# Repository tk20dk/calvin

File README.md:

# calvin
886 MHz Sensor module (CC1110)

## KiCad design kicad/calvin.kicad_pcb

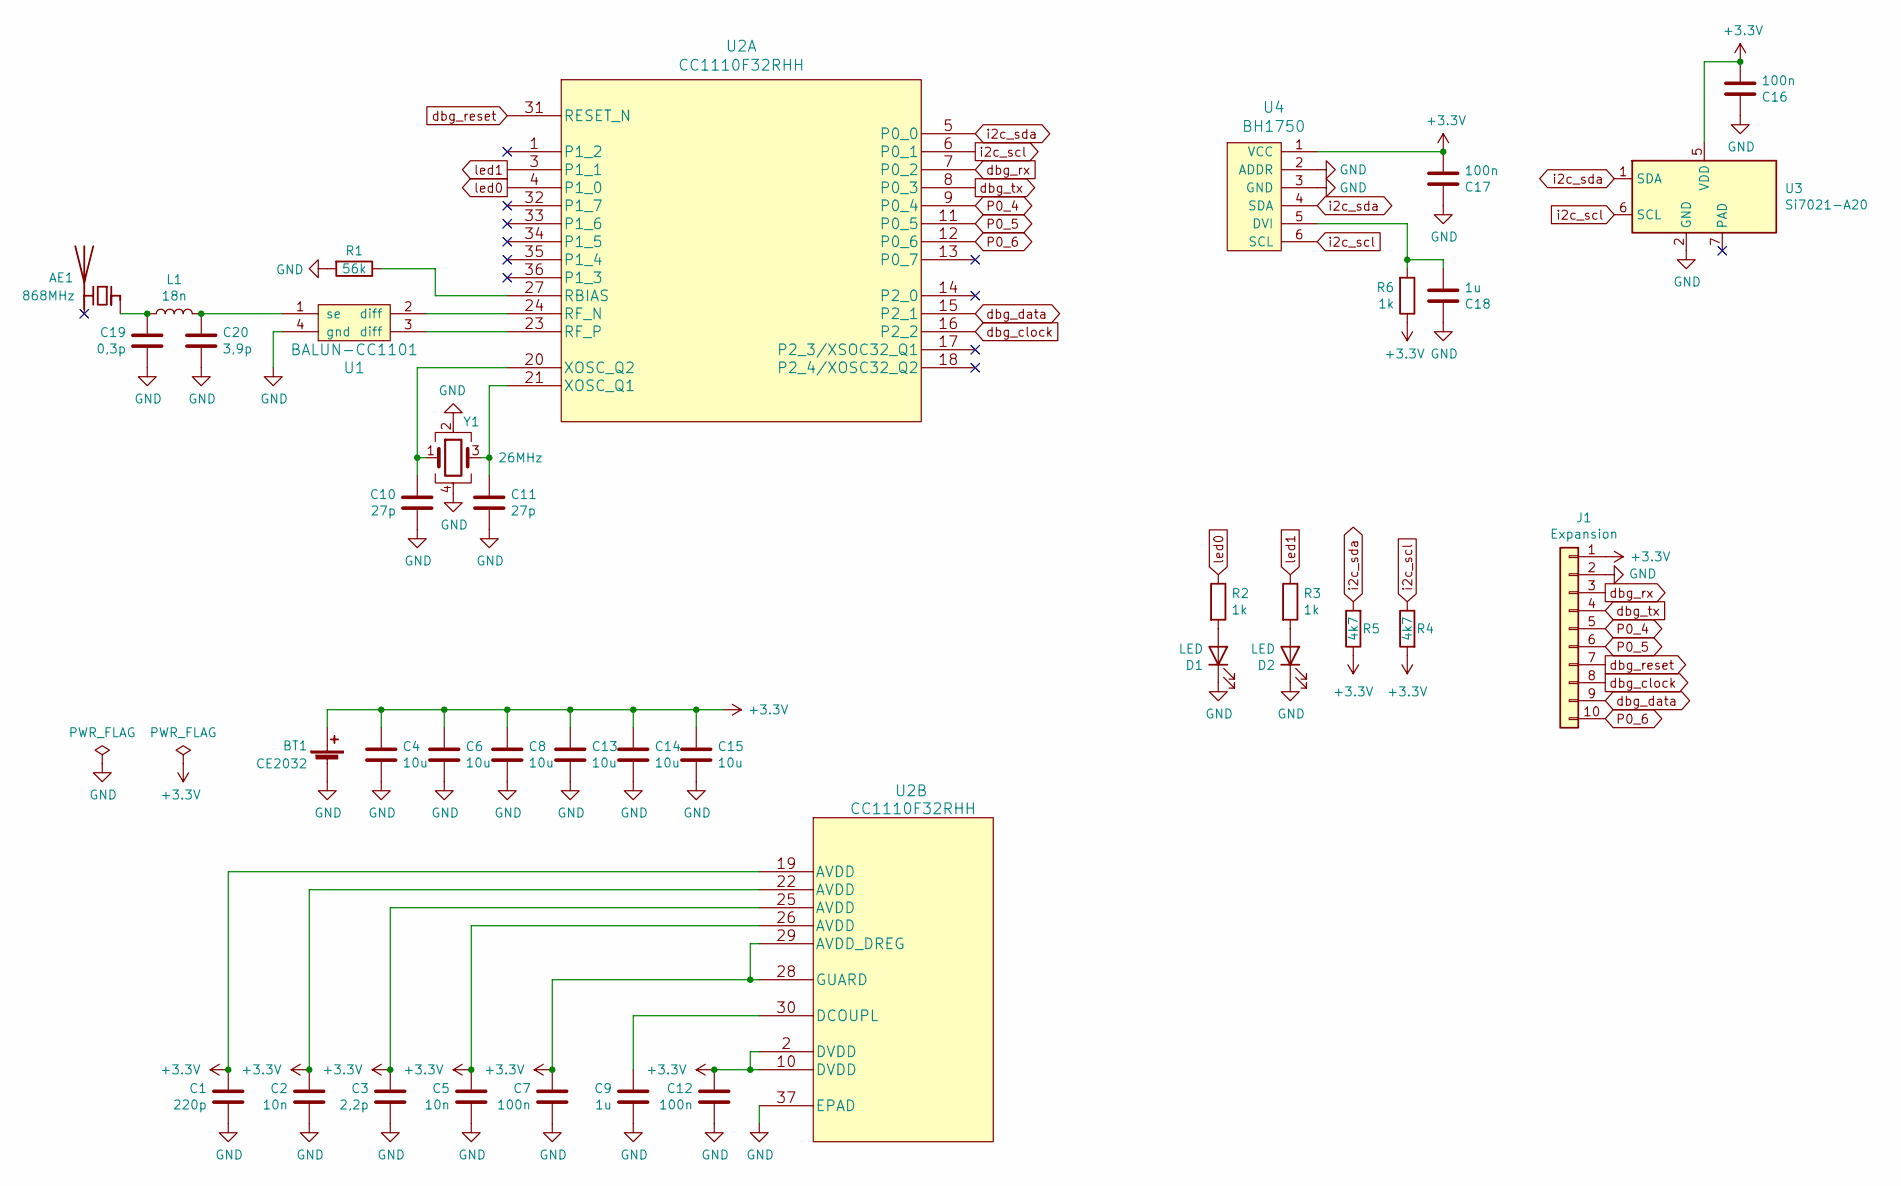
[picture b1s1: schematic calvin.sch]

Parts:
AE1: 868MHz; 0868AT43A0020
BT1: CE2032; CR2032_HOLDER_02
C1: 220p; C_0402_1005Metric
C2, C5: 10n; C_0402_1005Metric
C3: 2,2p; C_0402_1005Metric
C4, C6, C8, C13, C14, C15: 10u; C_0805_2012Metric
C7, C12, C16, C17: 100n; C_0402_1005Metric
C9, C18: 1u; C_0402_1005Metric
C10, C11: 27p; C_0402_1005Metric
C19: 0,3p; C_0402_1005Metric
C20: 3,9p; C_0402_1005Metric
D1, D2: LED; LED_0402_1005Metric
J1: Expansion; JST_SH_SM10B-SRSS-TB_1x10-1MP_P1.00mm_Horizontal
L1: 18n; L_0402_1005Metric
R1: 56k; R_0402_1005Metric
R2, R3, R6: 1k; R_0402_1005Metric
R4, R5: 4k7; R_0402_1005Metric
U1: BALUN-CC1101
U2: CC1110F32RHH; CC111x
U3: Si7021-A20; DFN-6-1EP_3x3mm_P1mm_EP1.5x2.4mm; LCSC C430231
U4: BH1750
Y1: 26MHz; Crystal_SMD_2016-4Pin_2.0x1.6mm; LCSC C1987154

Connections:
+3V3: BT1.1 (+), C1.1, C2.1, C3.1, C4.1, C5.1, C6.1, C7.1, C8.1, C12.1, C13.1, C14.1, C15.1, C16.2, C17.2, J1.1, R4.2, R5.1, R6.1, U2.2 (DVDD), U2.10 (DVDD), U2.19 (AVDD), U2.22 (AVDD), U2.25 (AVDD), U2.26 (AVDD), U2.28 (GUARD), U2.29 (AVDD_DREG), U3.5 (VDD), U4.1 (VCC)
GND: BT1.2 (-), C1.2, C2.2, C3.2, C4.2, C5.2, C6.2, C7.2, C8.2, C9.2, C10.1, C11.2, C12.2, C13.2, C14.2, C15.2, C16.1, C17.1, C18.1, C19.1, C20.2, D1.1 (K), D2.1 (K), J1.2, R1.2, U1.4 (gnd), U2.37 (EPAD), U3.2 (GND), U4.2 (ADDR), U4.3 (GND), Y1.2, Y1.4
unnamed: AE1.1 (FEED), C19.2, L1.1
unnamed: C9.1, U2.30 (DCOUPL)
unnamed: C10.2, U2.20 (XOSC_Q2), Y1.1
unnamed: C11.1, U2.21 (XOSC_Q1), Y1.3
unnamed: C18.2, R6.2, U4.5 (DVI)
unnamed: C20.1, L1.2, U1.1 (se)
unnamed: D1.2 (A), R2.2
unnamed: D2.2 (A), R3.2
unnamed: R1.1, U2.27 (RBIAS)
unnamed: U1.2 (diff), U2.24 (RF_N)
unnamed: U1.3 (diff), U2.23 (RF_P)
P0_4: J1.5, U2.9 (P0_4)
P0_5: J1.6, U2.11 (P0_5)
P0_6: J1.10, U2.12 (P0_6)
dbg_clock: J1.8, U2.16 (P2_2)
dbg_data: J1.9, U2.15 (P2_1)
dbg_reset: J1.7, U2.31 (RESET_N)
dbg_rx: J1.3, U2.7 (P0_2)
dbg_tx: J1.4, U2.8 (P0_3)
i2c_scl: R4.1, U2.6 (P0_1), U3.6 (SCL), U4.6 (SCL)
i2c_sda: R5.2, U2.5 (P0_0), U3.1 (SDA), U4.4 (SDA)
led0: R2.1, U2.4 (P1_0)
led1: R3.1, U2.3 (P1_1)

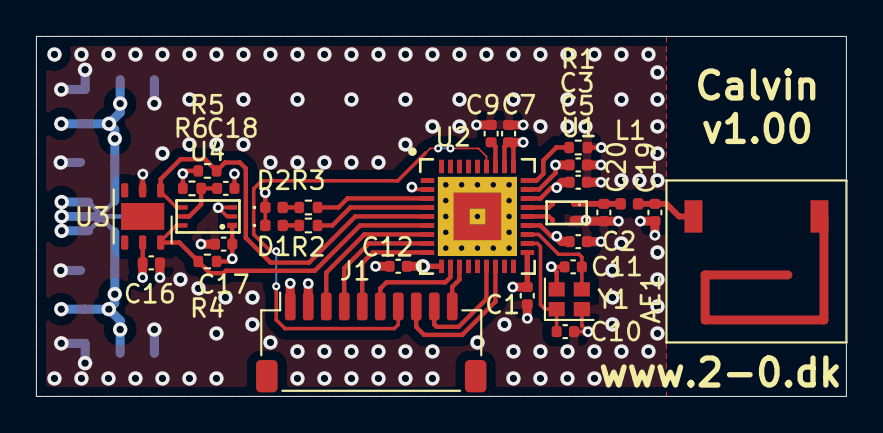
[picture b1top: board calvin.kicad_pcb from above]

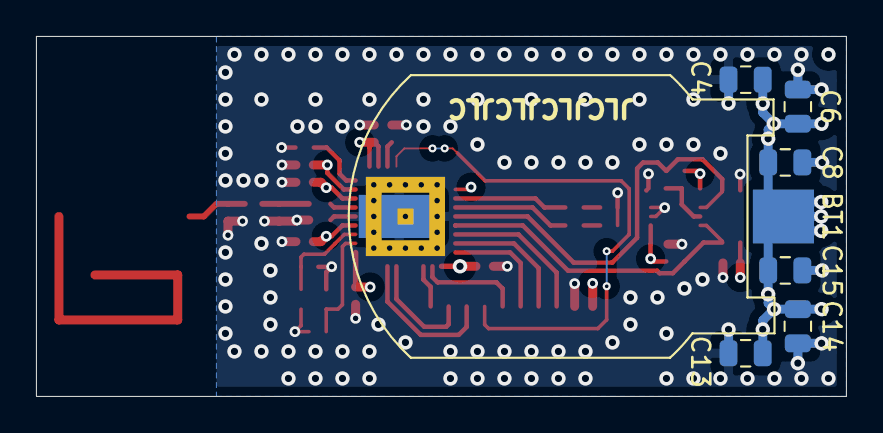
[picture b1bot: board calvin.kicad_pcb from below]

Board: 4 copper layers, 45.0 x 20.0 mm, 37 parts (7 on the bottom side), 25 nets.

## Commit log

2021-03-27 v1.00 ready for review
2021-04-11 calvin_v1.00
